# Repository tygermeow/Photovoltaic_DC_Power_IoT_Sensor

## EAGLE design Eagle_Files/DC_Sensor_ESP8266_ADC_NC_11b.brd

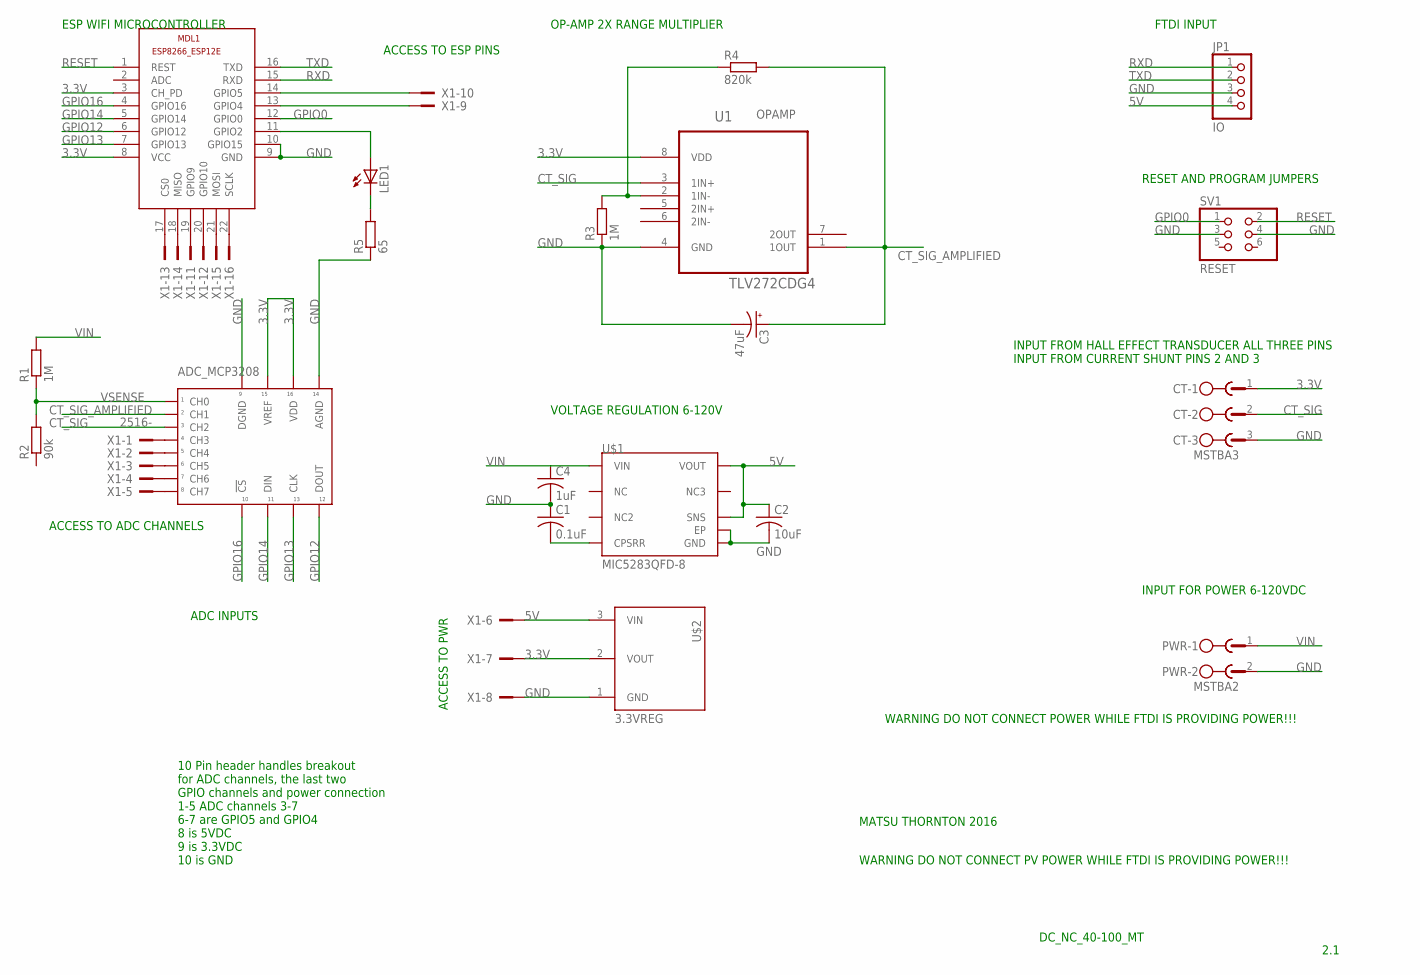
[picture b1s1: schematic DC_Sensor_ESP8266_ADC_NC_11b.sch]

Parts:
ADC_MCP3208: 21298ESMD; PDIP16
C1: 0.1uF; C0402; MFG# GRM155R71C104KA88J
C2: 10uF; C0603K
C3: 47uF; PANASONIC_C
C4: 1uF; C2220K; MFG# C5750X7R2E105M230KA
CT: MSTBA3
JP1: IO; 1X04
LED1: LEDCHIP-LED0603; CHIP-LED0603
MDL1: ESP8266-12EESP8266-ESP12E; ESP8266-ESP12E
PWR: MSTBA2
R1, R3: 1M; R0805
R2: 90k; R0805
R4: 820k; R0805
R5: 65; R0805
SV1: RESET; 2X03
U1: TLV272CDG4; SOIC127P600X175-8N
U$1: MIC5283QFD-8; 8-VDFN
U$2: 3.3VREG; 3PVREG
X1: 2516-; PAK100/2500-16

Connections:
3.3V: ADC_MCP3208.P$15 (VREF), ADC_MCP3208.P$16 (VDD), CT.1, MDL1.3 (CH_PD), MDL1.8 (VCC), U1.8 (VDD), U$2.2 (VOUT), X1.7
5V: C2.1, JP1.4, U$1.P$6 (SNS), U$1.P$8 (VOUT), U$2.3 (VIN), X1.6
CT_SIG: ADC_MCP3208.P$3 (CH2), CT.2, U1.3 (1IN+)
CT_SIG_AMPLIFIED: ADC_MCP3208.P$2 (CH1), C3.+, R4.2, U1.1 (1OUT)
GND: ADC_MCP3208.P$9 (DGND), ADC_MCP3208.P$14 (AGND), C1.1, C2.2, C3.-, C4.2, CT.3, JP1.3, MDL1.9 (GND), MDL1.10 (GPIO15), PWR.2, R3.1, R5.1, SV1.3, SV1.4, U1.4 (GND), U$1.EXP (EP), U$1.P$5 (GND), U$2.1 (GND), X1.8
GPIO0: MDL1.12 (GPIO0), SV1.1
GPIO4: MDL1.13 (GPIO4), X1.9
GPIO5: MDL1.14 (GPIO5), X1.10
GPIO12: ADC_MCP3208.P$12 (DOUT), MDL1.6 (GPIO12)
GPIO13: ADC_MCP3208.P$13 (CLK), MDL1.7 (GPIO13)
GPIO14: ADC_MCP3208.P$11 (DIN), MDL1.5 (GPIO14)
GPIO16: ADC_MCP3208.P$10 (!CS), MDL1.4 (GPIO16)
unnamed: LED1.A, MDL1.11 (GPIO2)
unnamed: R3.2, R4.1, U1.2 (1IN-)
unnamed: LED1.C, R5.2
unnamed: C1.2, U$1.P$4 (CPSRR)
unnamed: ADC_MCP3208.P$4 (CH3), X1.1
unnamed: ADC_MCP3208.P$5 (CH4), X1.2
unnamed: ADC_MCP3208.P$6 (CH5), X1.3
unnamed: ADC_MCP3208.P$7 (CH6), X1.4
unnamed: ADC_MCP3208.P$8 (CH7), X1.5
unnamed: MDL1.19 (GPIO9), X1.11
unnamed: MDL1.20 (GPIO10), X1.12
unnamed: MDL1.17 (CS0), X1.13
unnamed: MDL1.18 (MISO), X1.14
unnamed: MDL1.21 (MOSI), X1.15
unnamed: MDL1.22 (SCLK), X1.16
RESET: MDL1.1 (REST), SV1.2
RXD: JP1.1, MDL1.15 (RXD)
TXD: JP1.2, MDL1.16 (TXD)
VIN: C4.1, PWR.1, R1.2, U$1.P$1 (VIN)
VSENSE: ADC_MCP3208.P$1 (CH0), R1.1, R2.2

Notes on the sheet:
DC_NC_40-100_MT
2.1
MATSU THORNTON 2016
VOLTAGE REGULATION 6-120V
OP-AMP 2X RANGE MULTIPLIER
FTDI INPUT
RESET AND PROGRAM JUMPERS
INPUT FROM HALL EFFECT TRANSDUCER ALL THREE PINS INPUT FROM CURRENT SHUNT PINS 2 AND 3
INPUT FOR POWER 6-120VDC
WARNING DO NOT CONNECT PV POWER WHILE FTDI IS PROVIDING POWER!!!
WARNING DO NOT CONNECT POWER WHILE FTDI IS PROVIDING POWER!!!
ESP WIFI MICROCONTROLLER
ADC INPUTS
ACCESS TO ESP PINS
ACCESS TO ADC CHANNELS
ACCESS TO PWR
10 Pin header handles breakout for ADC channels, the last two GPIO channels and power connection 1-5 ADC channels 3-7 6-7 are GPIO5 and GPIO4 8 is 5VDC 9 is 3.3VDC 10 is GND

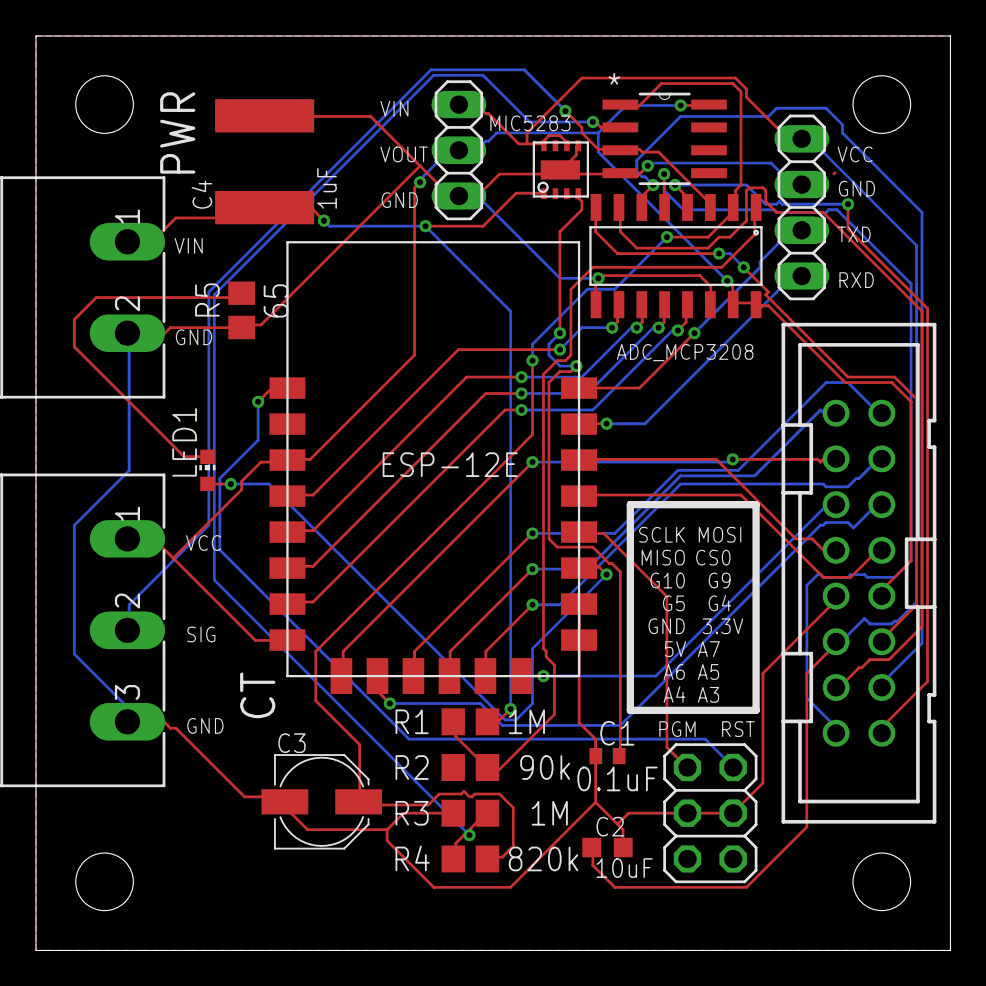
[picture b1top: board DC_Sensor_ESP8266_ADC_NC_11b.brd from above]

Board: 2 copper layers, 50.8 x 50.8 mm, 20 parts (0 on the bottom side), 32 nets.

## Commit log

2016-05-05 Start of DC Sensor Code
2016-05-05 Added files via upload
2016-05-05 Rename DC_Sensor.ino to DC_Sensor_v1.2.ino
    No 1 second for loop, getting ready to change over to variable time requests from master unit and report average power over whatever period happens between requests.
2016-05-05 Added files via upload
    Original with one second interval for for loop collecting sample data
2016-05-05 Placed Slave Sensor files into the ATmega328_SensorInput folder. This is the slave sender under I2C
2016-05-05 This update gives the average power for the sample period between requests from the wifi master sender. The time period sampled over is not necessarily uniform but is an average for that period which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
2016-05-07 ESP8266 sister board sender files added.
    Prototype is still non-functional
2016-05-31 DC sensor based on a non-contact hall effect sensor. Will regulate from 0-40VDC. Update of files includes a link to onenote development documentation. Also includes outline template of baseplate for 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
2016-05-31 Archive old documents
2016-06-30 Updated to latest 11b ribbon board
